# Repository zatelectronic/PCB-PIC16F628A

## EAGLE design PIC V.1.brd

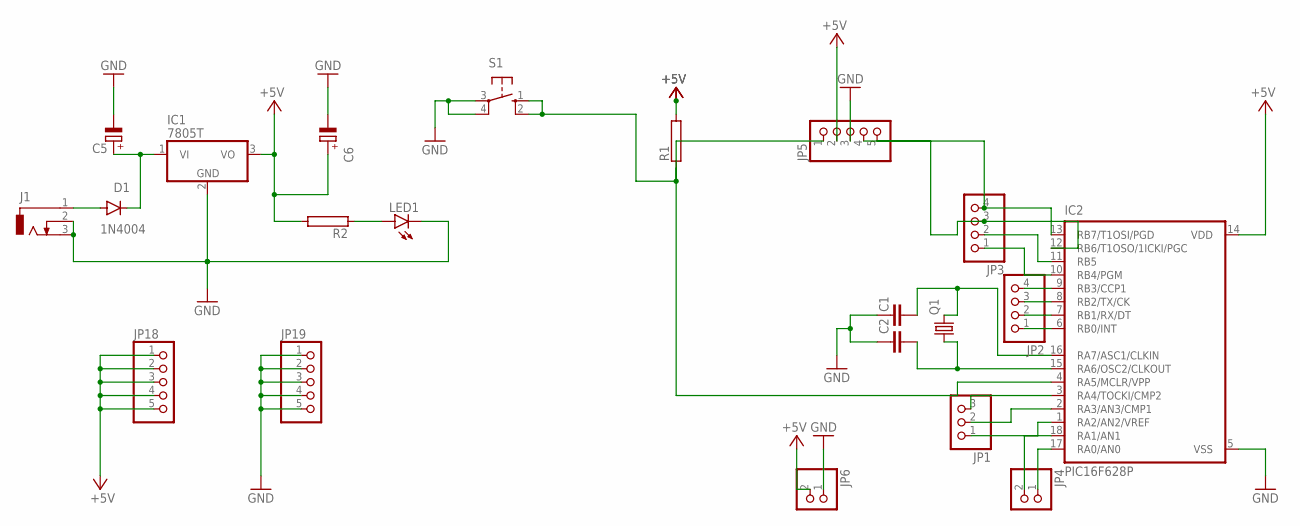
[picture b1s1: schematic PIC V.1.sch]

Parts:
C1, C2: C2.5/2; C2.5-2
C5, C6: CPOL-EUE2,5-6E; E2,5-6E
D1: 1N4004; DO41-10
IC1: 7805T; TO220H
IC2: PIC16F628P; DIL18
J1: DCJ0303
JP1: PINHD-1X3; 1X03
JP2, JP3: PINHD-1X4; 1X04
JP4, JP6: PINHD-1X2; 1X02
JP5, JP18, JP19: PINHD-1X5; 1X05
LED1: LED5MM
Q1: CRYSTALHC49U-V; HC49U-V
R1, R2: RRS1/4; RS1/4
S1: 10-XX; B3F-10XX

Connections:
+5V: C6.+, IC1.3 (VO), IC2.14 (VDD), JP5.2, JP6.2, JP18.1, JP18.2, JP18.3, JP18.4, JP18.5, R1.2, R2.2
GND: C1.1, C2.1, C5.-, C6.-, IC1.2 (GND), IC2.5 (VSS), J1.2, J1.3, JP5.3, JP6.1, JP19.1, JP19.2, JP19.3, JP19.4, JP19.5, LED1.K (C), S1.3, S1.4 (P1)
unnamed: IC2.1 (RA2/AN2/VREF), JP1.1
unnamed: IC2.2 (RA3/AN3/CMP1), JP1.2
unnamed: IC2.3 (RA4/TOCKI/CMP2), JP1.3
unnamed: IC2.6 (RB0/INT), JP2.1
unnamed: IC2.7 (RB1/RX/DT), JP2.2
unnamed: IC2.8 (RB2/TX/CK), JP2.3
unnamed: IC2.9 (RB3/CCP1), JP2.4
unnamed: IC2.10 (RB4/PGM), JP3.1
unnamed: IC2.11 (RB5), JP3.2
unnamed: IC2.12 (RB6/T1OSO/1ICKI/PGC), JP3.3, JP5.5
unnamed: IC2.13 (RB7/T1OSI/PGD), JP3.4, JP5.4
unnamed: IC2.17 (RA0/AN0), JP4.1
unnamed: IC2.18 (RA1/AN1), JP4.2
unnamed: C2.2, IC2.15 (RA6/OSC2/CLKOUT), Q1.1
unnamed: IC2.4 (RA5/MCLR/VPP), JP5.1, R1.1, S1.1 (S), S1.2 (S1)
unnamed: C1.2, IC2.16 (RA7/ASC1/CLKIN), Q1.2
unnamed: C5.+, D1.C, IC1.1 (VI)
unnamed: LED1.A, R2.1
unnamed: D1.A, J1.1

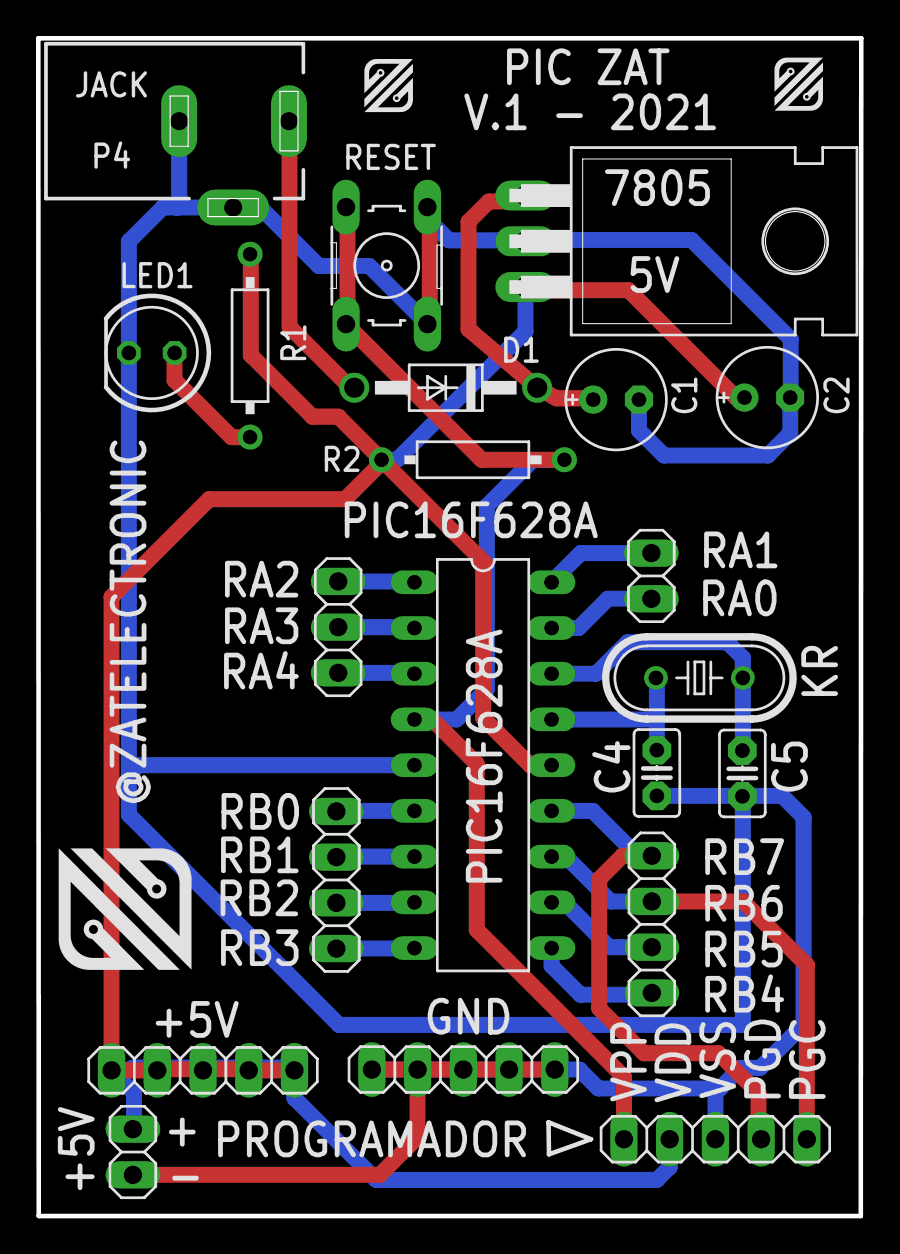
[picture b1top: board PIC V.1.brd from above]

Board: 2 copper layers, 45.7 x 65.4 mm, 24 parts (0 on the bottom side), 21 nets.

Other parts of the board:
U$1: LOGO_ZATELECTRONIC1.25CM
U$2, U$3: SIMBOLO_PEQUENO

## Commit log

2021-10-25 PRIMEIRO ENVIO
